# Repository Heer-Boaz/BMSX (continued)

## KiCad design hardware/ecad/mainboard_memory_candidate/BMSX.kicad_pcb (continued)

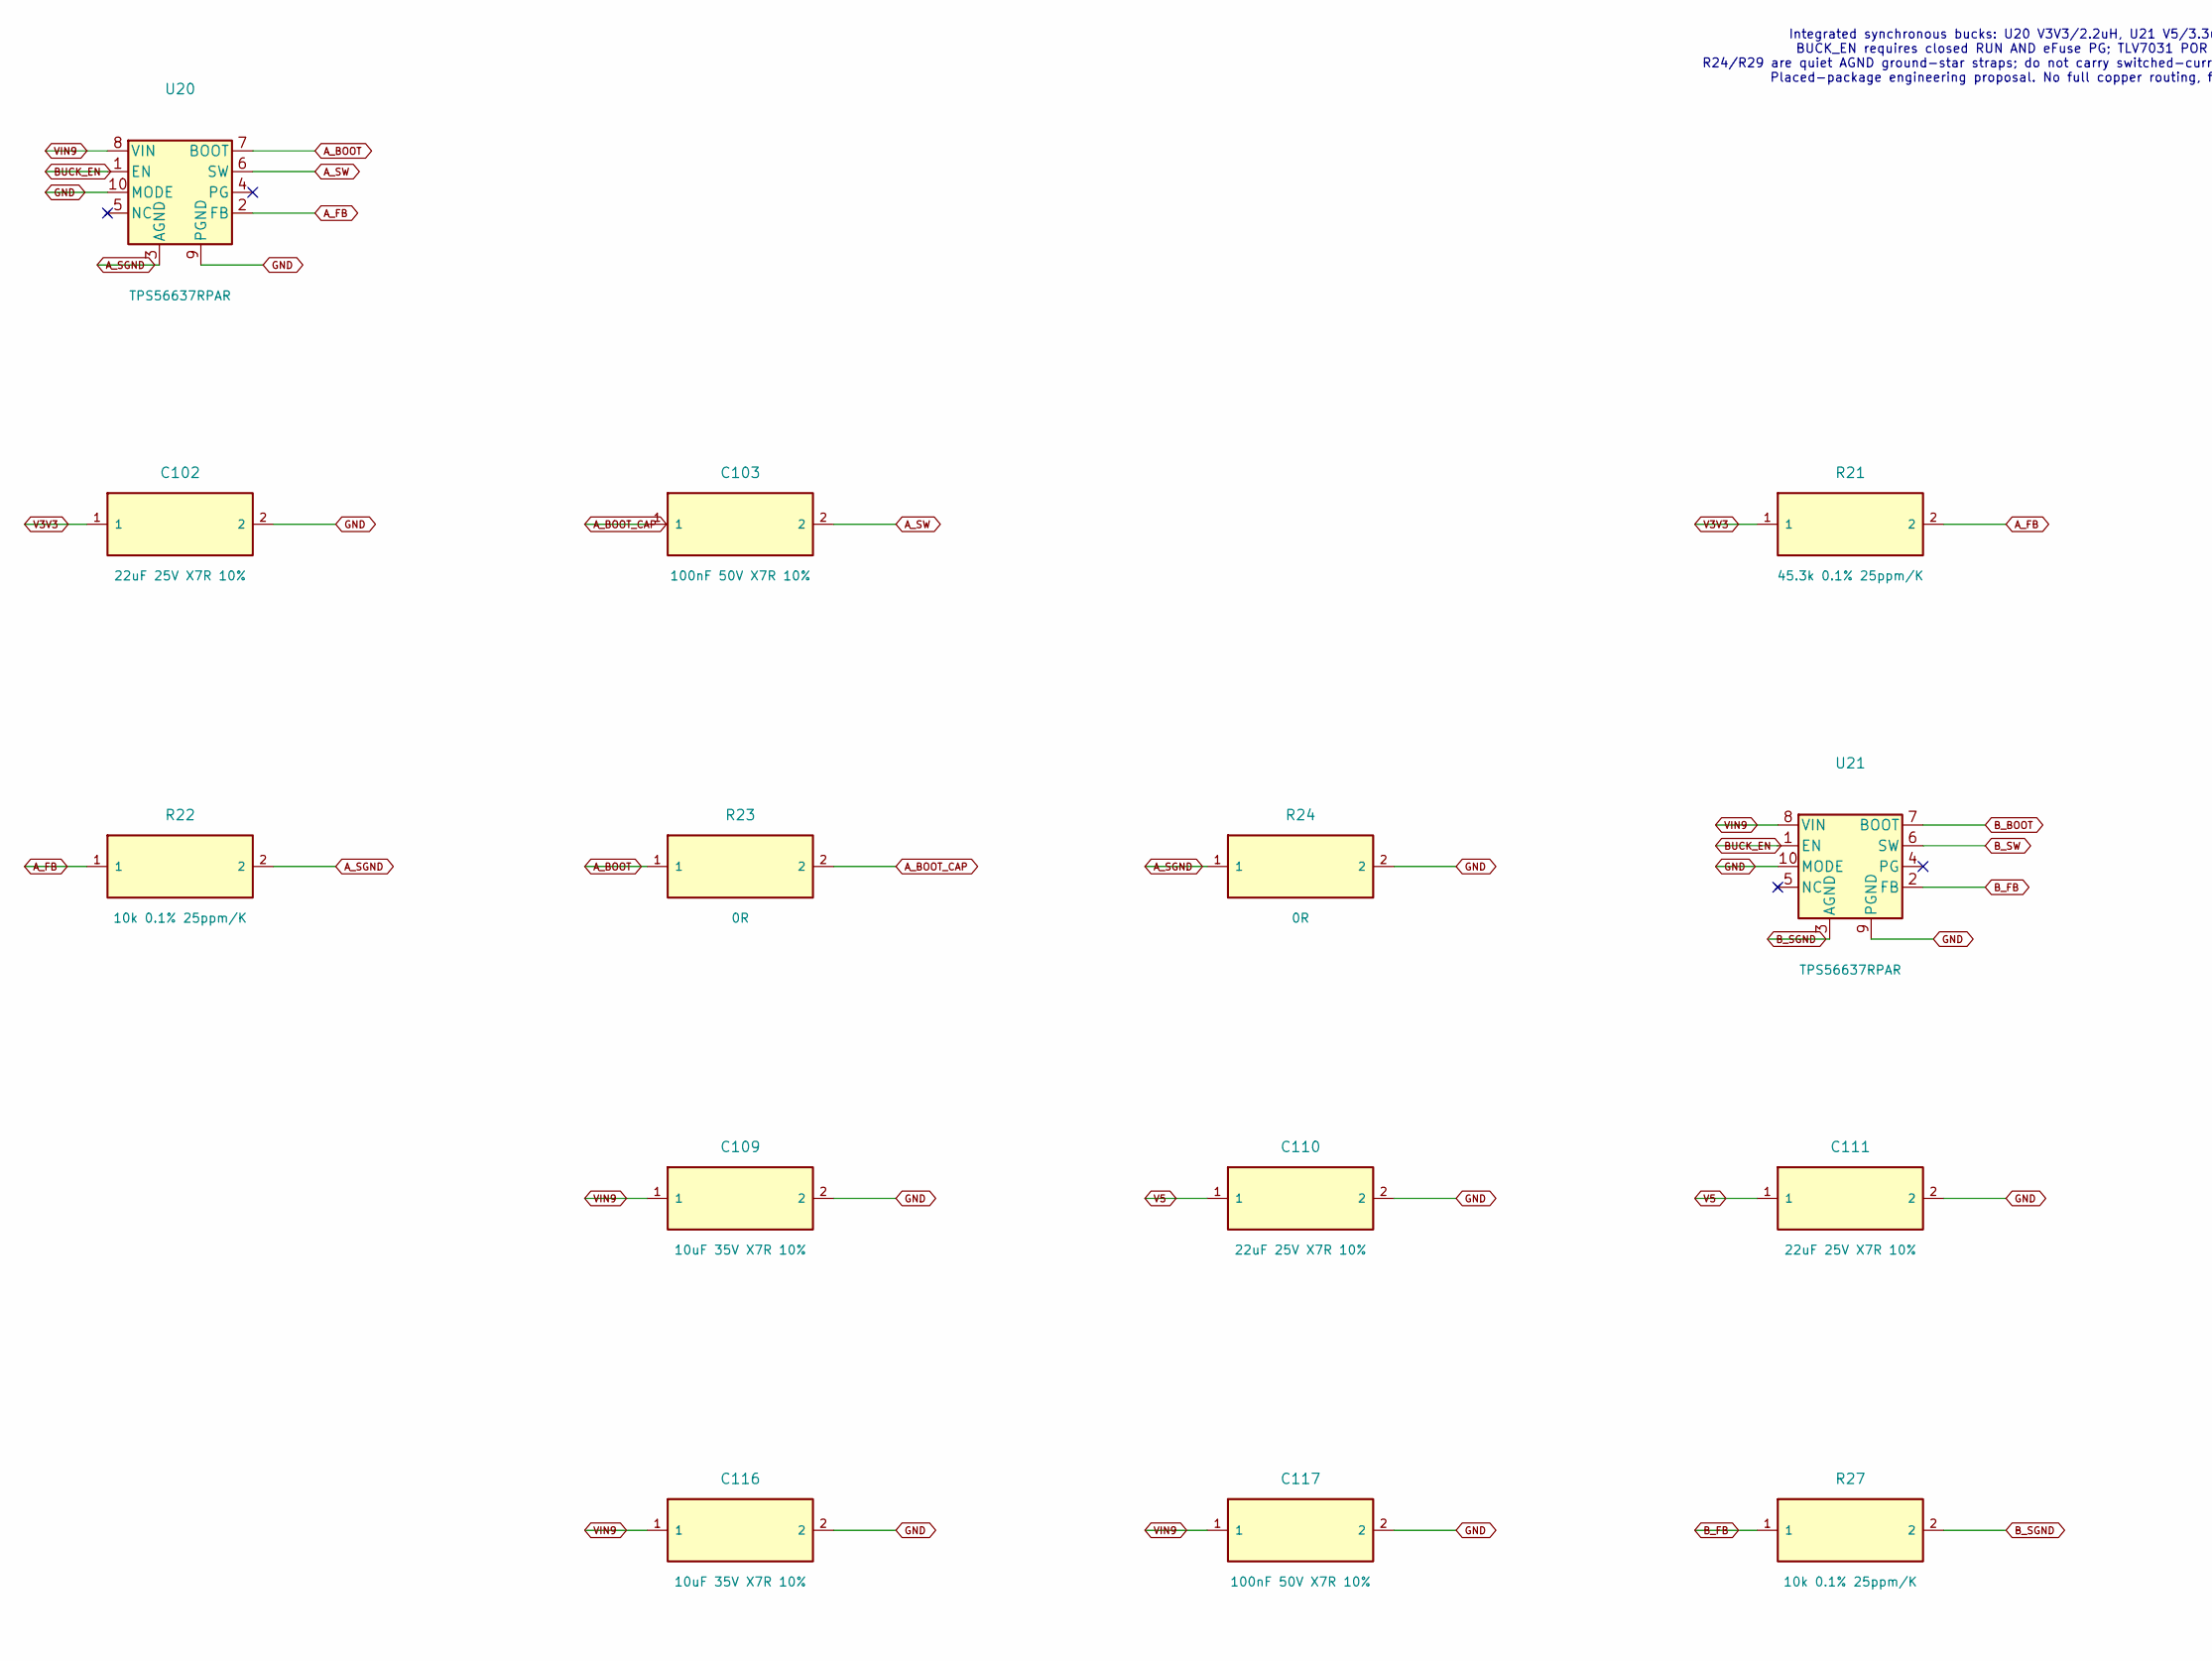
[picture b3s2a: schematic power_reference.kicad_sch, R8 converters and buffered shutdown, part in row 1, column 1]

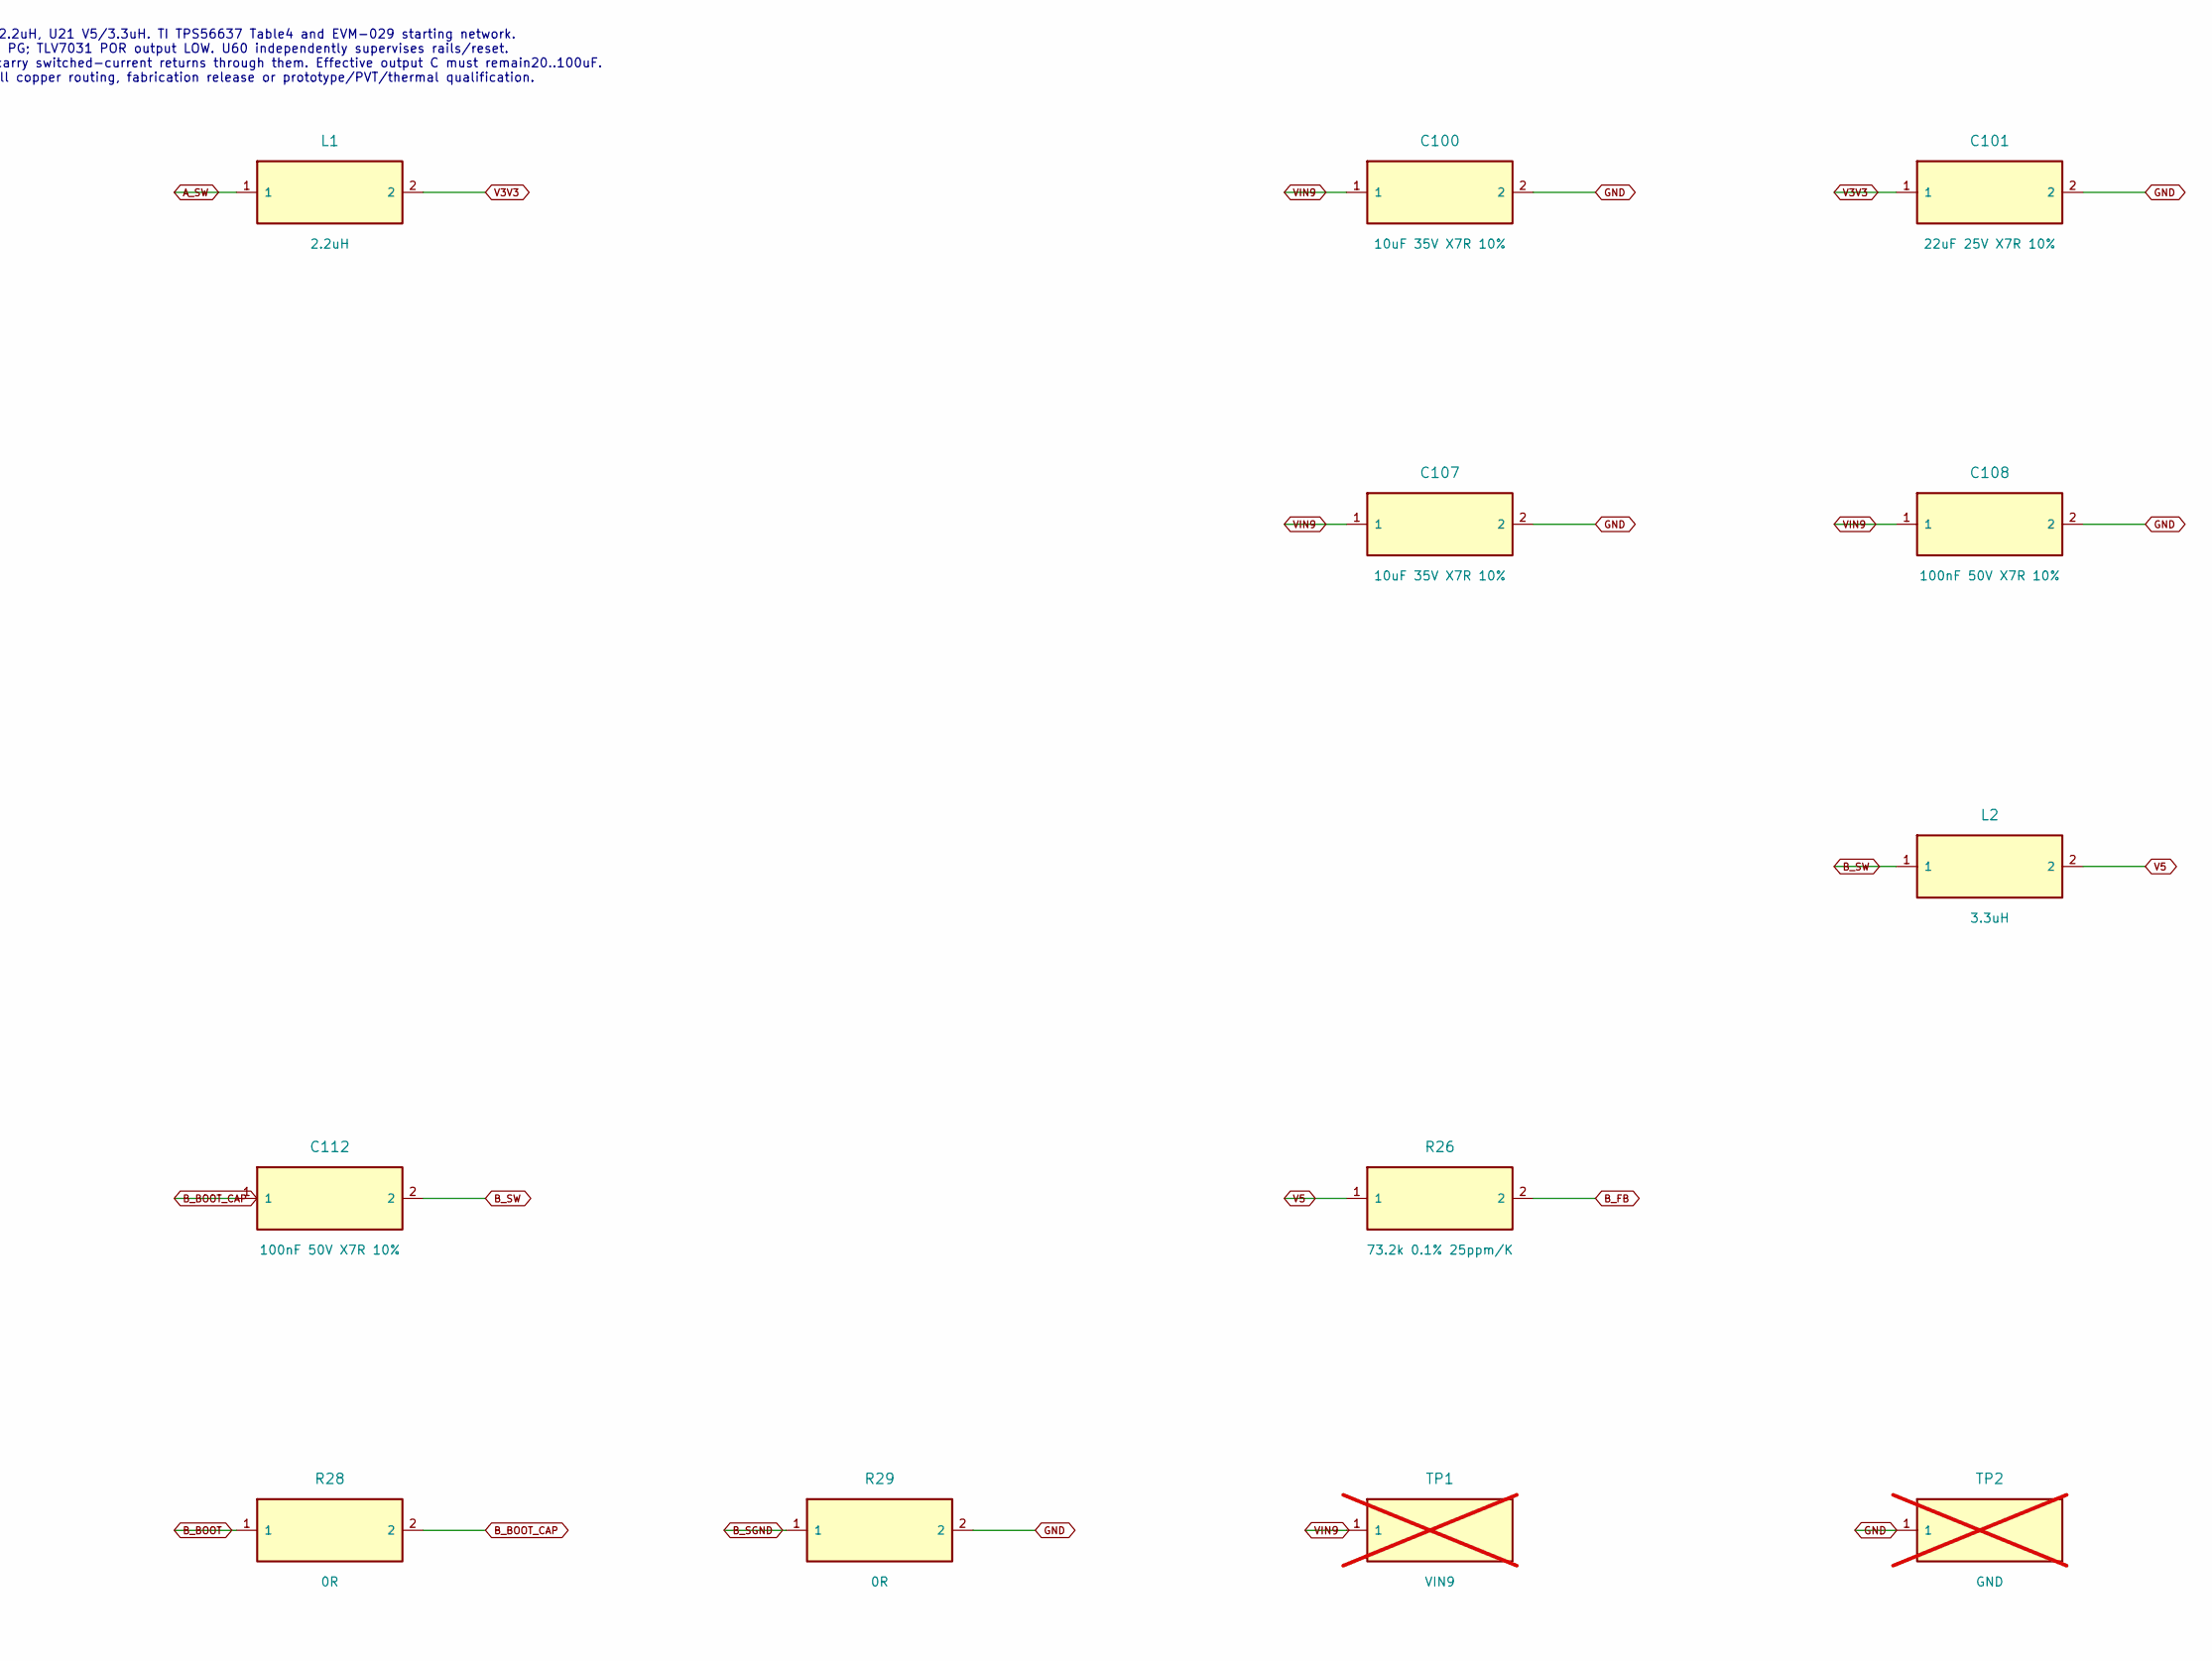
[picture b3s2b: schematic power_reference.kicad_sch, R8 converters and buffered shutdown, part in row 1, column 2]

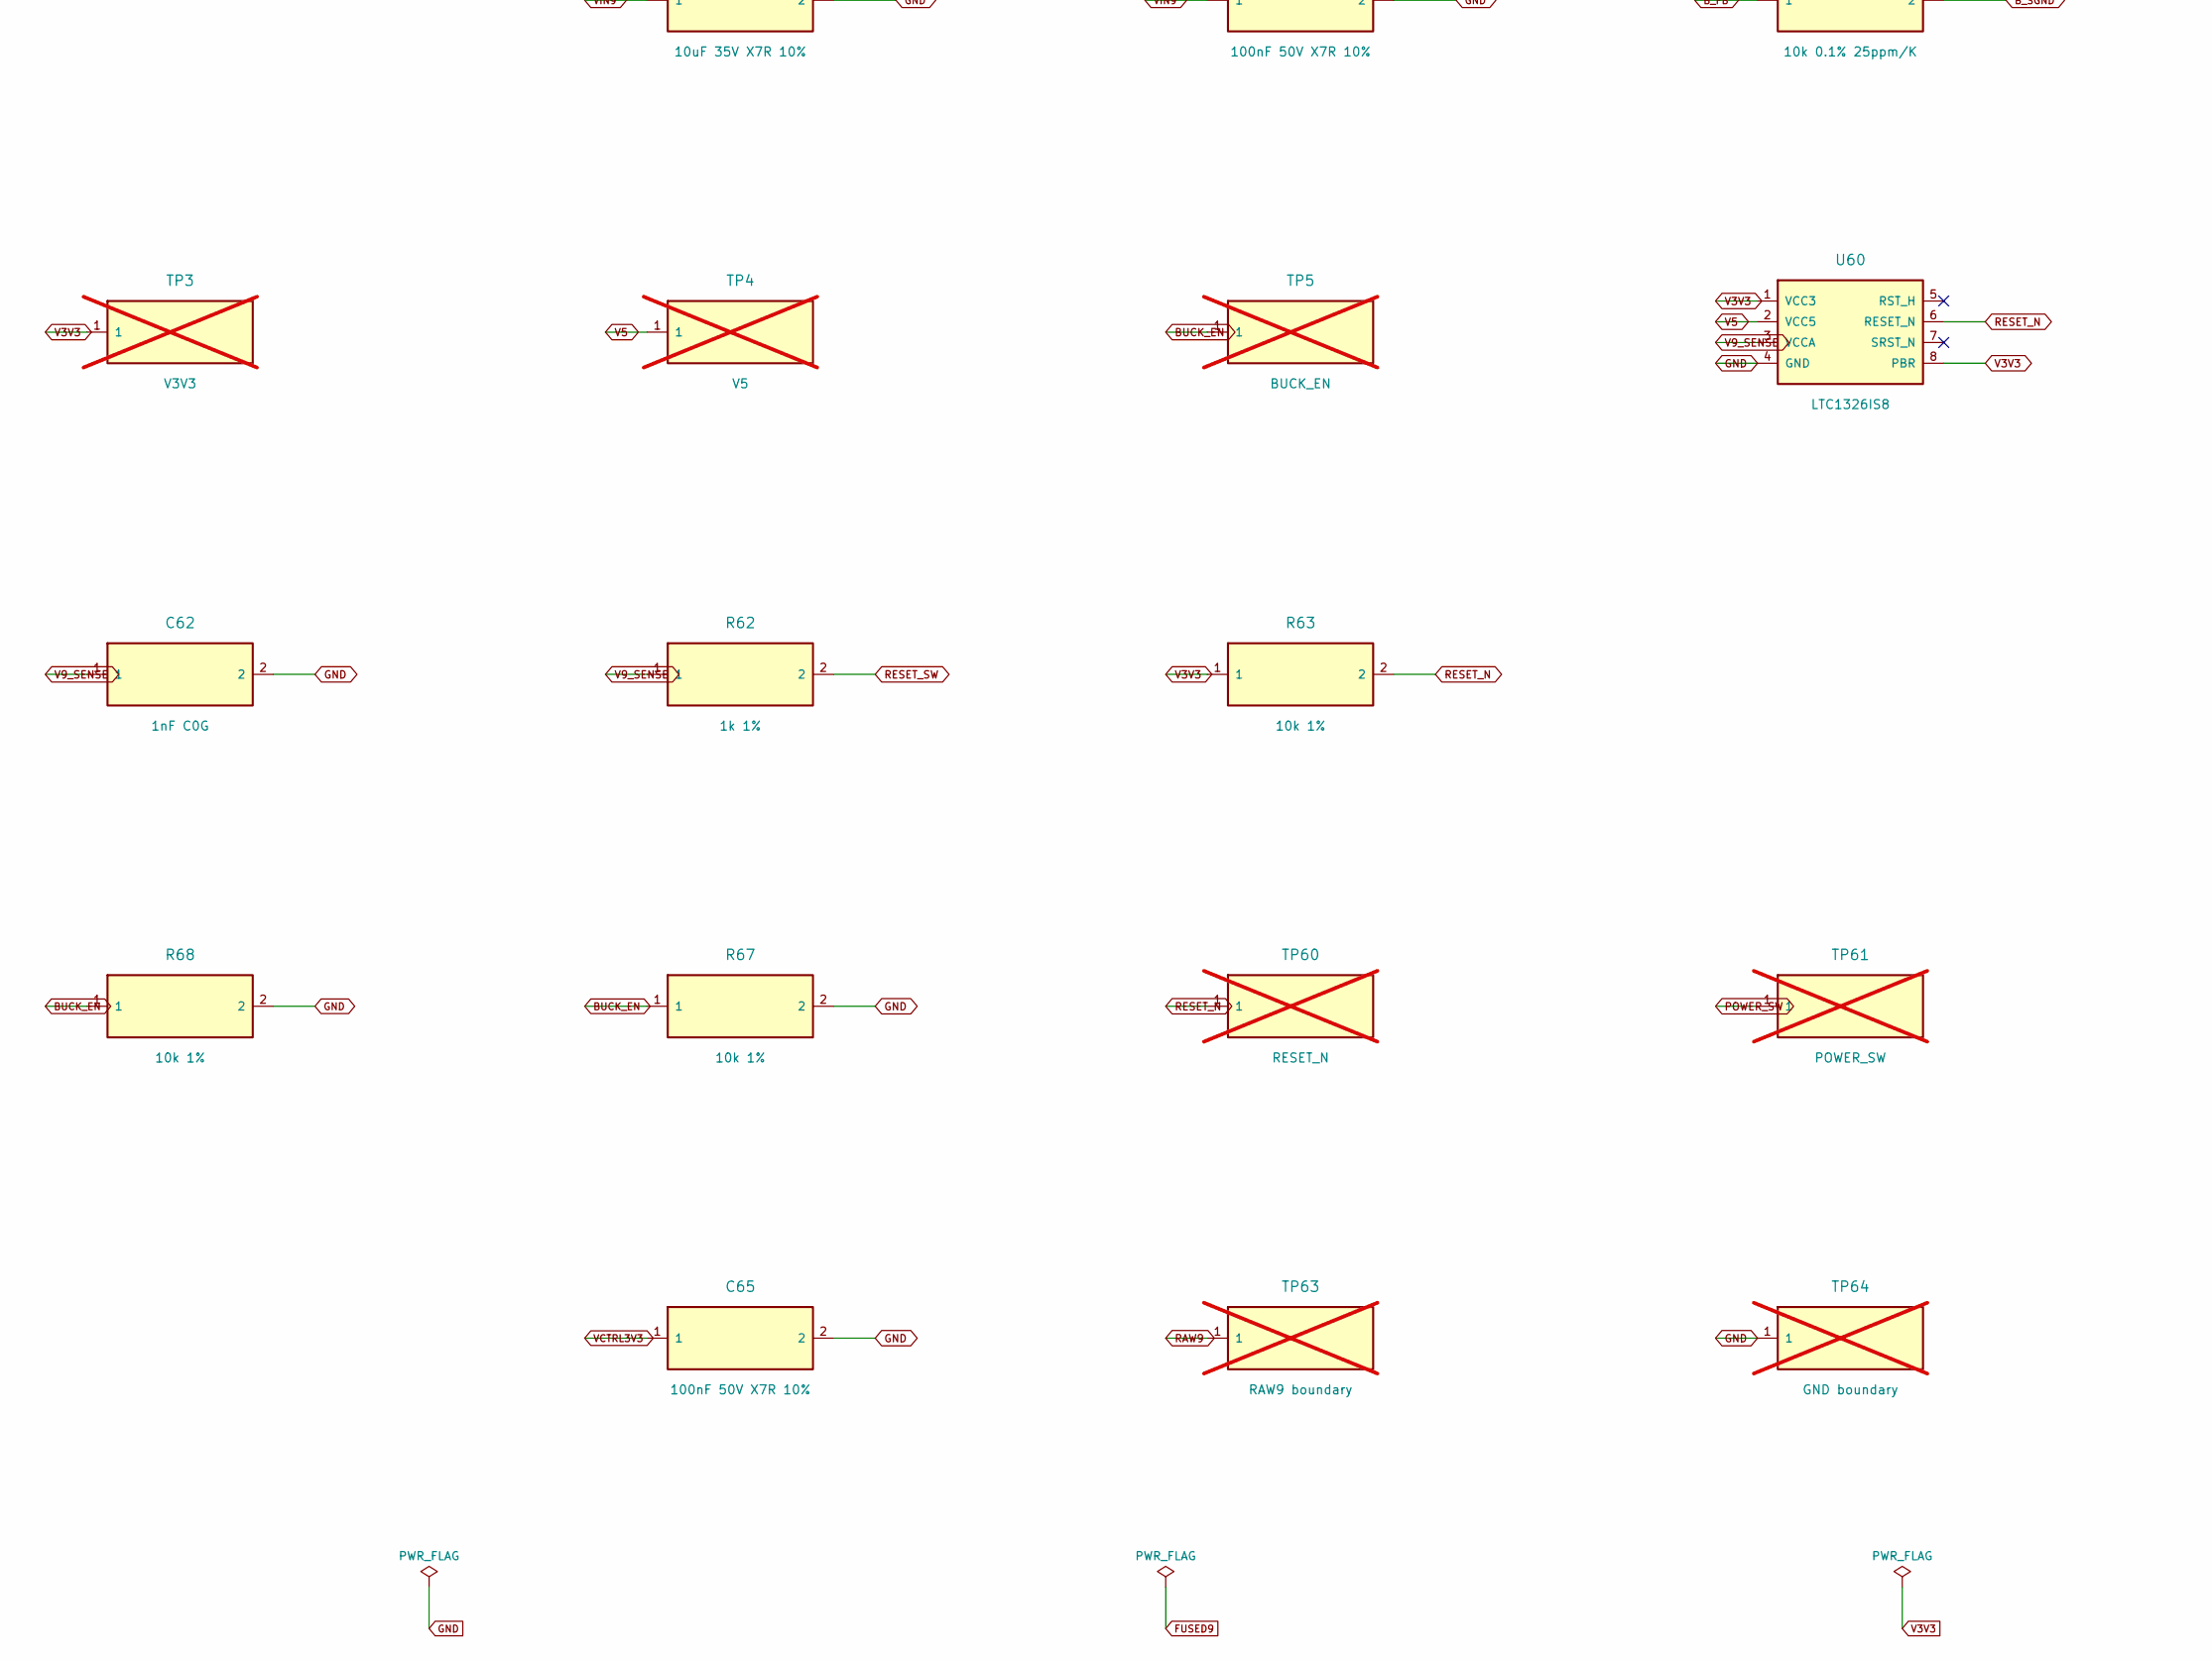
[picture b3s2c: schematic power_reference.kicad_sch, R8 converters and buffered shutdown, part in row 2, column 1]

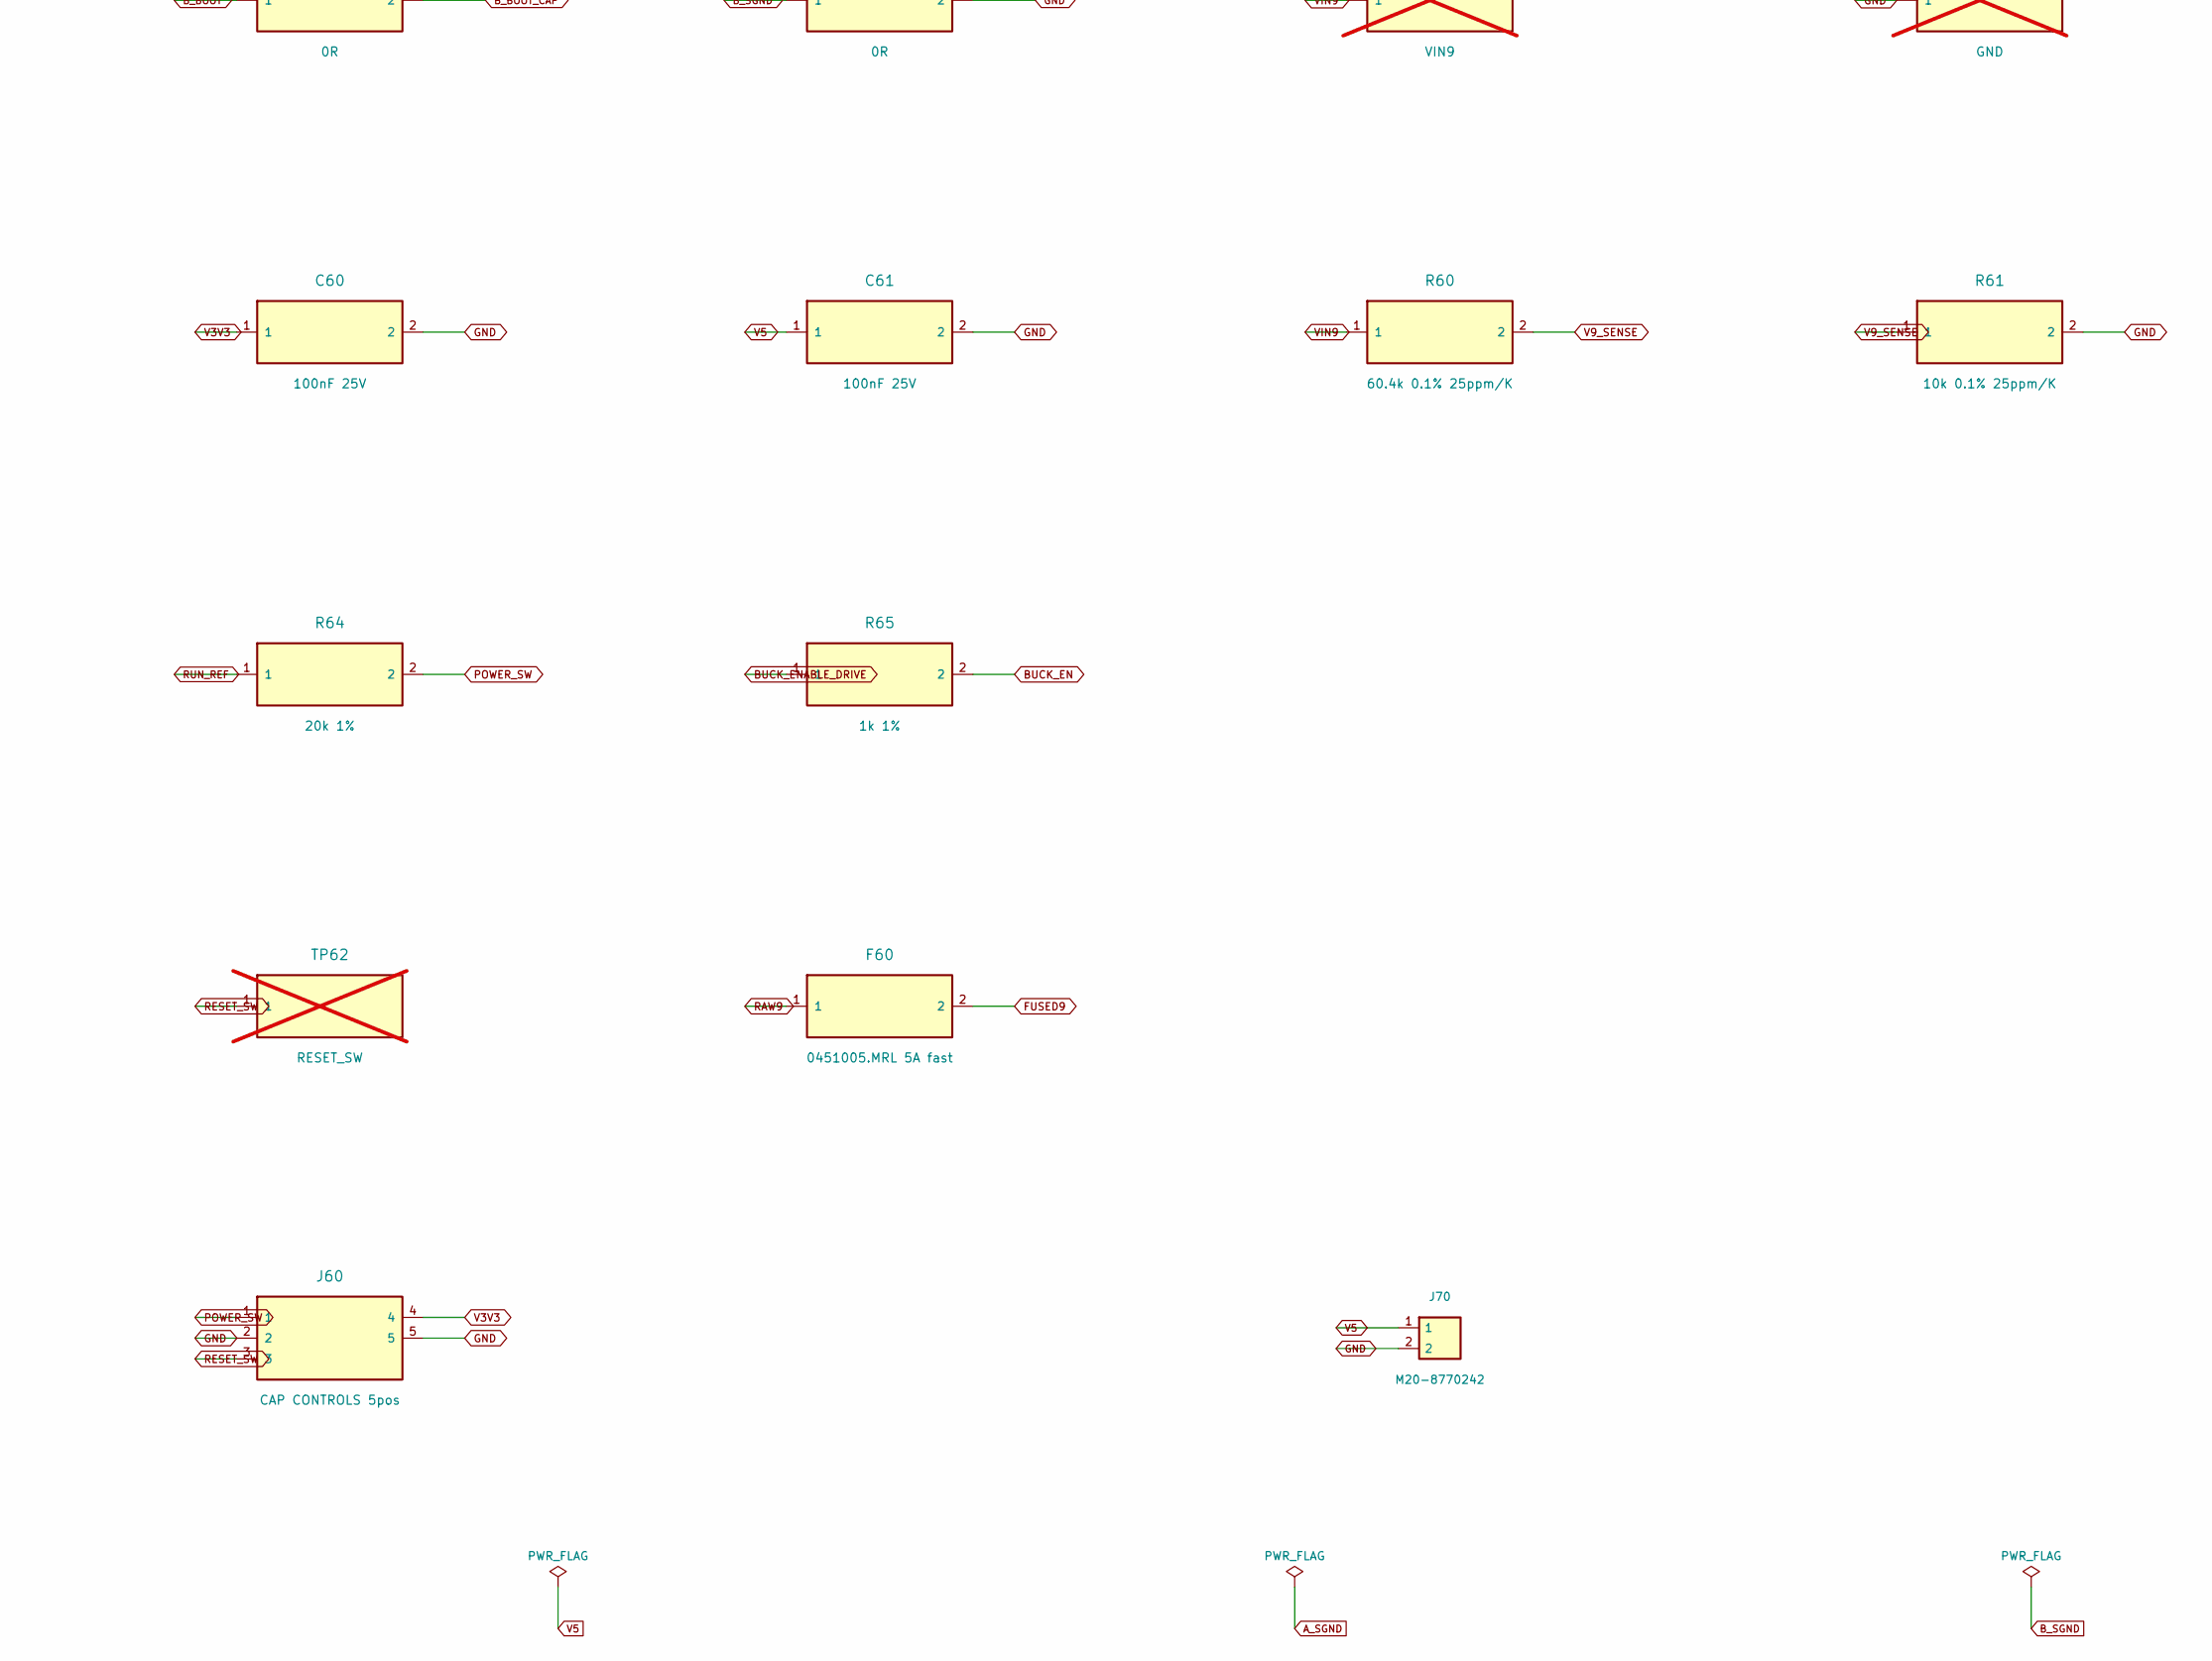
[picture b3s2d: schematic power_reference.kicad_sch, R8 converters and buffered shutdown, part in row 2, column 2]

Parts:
C60, C61: 100nF 25V; CL10B104KA8NNNC_retained_0603; MPN CL10B104KA8NNNC
C62: 1nF C0G; CL10C102JB8NNNC_retained_0603; MPN CL10C102JB8NNNC
C65: 100nF 50V X7R 10%; CL21B104KBCNNNC; MPN CL21B104KBCNNNC
C100, C107, C109, C116: 10uF 35V X7R 10%; C_1210_3225Metric; MPN GRM32ER7YA106KA12L
C101, C102, C110, C111: 22uF 25V X7R 10%; C_1210_3225Metric; MPN GRM32ER71E226KE15L
C103, C108, C112, C117: 100nF 50V X7R 10%; C_0603_1608Metric; MPN 885012206095
F60: 0451005.MRL 5A fast; F60
J60: CAP CONTROLS 5pos; J60; MPN M20-9770542
J70: M20-8770242; Harwin_M20-8770242; MPN M20-8770242
L1: 2.2uH; L_Vishay_IHLP-3232; MPN IHLP3232DZER2R2M11
L2: 3.3uH; L_Vishay_IHLP-3232; MPN IHLP3232DZER3R3M11
R21: 45.3k 0.1% 25ppm/K; TNPW0603_Vishay_28950; MPN TNPW060345K3BEEA
R22, R27, R61: 10k 0.1% 25ppm/K; TNPW0603_Vishay_28950; MPN TNPW060310K0BEEA
R23, R24, R28, R29: 0R; Yageo_RC0603_retained; MPN CRCW06030000Z0EA
R26: 73.2k 0.1% 25ppm/K; TNPW0603_Vishay_28950; MPN TNPW060373K2BEEA
R60: 60.4k 0.1% 25ppm/K; TNPW0603_Vishay_28950; MPN TNPW060360K4BEEA
R62, R65: 1k 1%; Yageo_RC0603_retained; MPN RC0603FR-071KL
R63, R67, R68: 10k 1%; Yageo_RC0603_retained; MPN RC0603FR-0710KL
R64: 20k 1%; Yageo_RC0603_retained; MPN RC0603FR-0720KL
TP1: VIN9; TP1; not fitted
TP2: GND; TP2; not fitted
TP3: V3V3; TP3; not fitted
TP4: V5; TP4; not fitted
TP5: BUCK_EN; TP5; not fitted
TP60: RESET_N; TP60; not fitted
TP61: POWER_SW; TP61; not fitted
TP62: RESET_SW; TP62; not fitted
TP63: RAW9 boundary; TP63; not fitted
TP64: GND boundary; TP64; not fitted
U20, U21: TPS56637RPAR; TPS56637RPAR_RPA0010A; MPN TPS56637RPAR
U60: LTC1326IS8; LTC1326IS8_PBF_S8_retained_IPC; MPN LTC1326IS8#PBF

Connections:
A_BOOT: R23.1, U20.7 (BOOT)
A_BOOT_CAP: C103.1, R23.2
A_FB: R21.2, R22.1, U20.2 (FB)
A_SGND: R22.2, R24.1, U20.3 (AGND)
A_SW: C103.2, L1.1, U20.6 (SW)
BUCK_EN: R65.2, R67.1, R68.1, TP5.1, U20.1 (EN), U21.1 (EN)
BUCK_ENABLE_DRIVE: R65.1; also elsewhere on the board
B_BOOT: R28.1, U21.7 (BOOT)
B_BOOT_CAP: C112.1, R28.2
B_FB: R26.2, R27.1, U21.2 (FB)
B_SGND: R27.2, R29.1, U21.3 (AGND)
B_SW: C112.2, L2.1, U21.6 (SW)
FUSED9: F60.2; also elsewhere on the board
GND: C60.2, C61.2, C62.2, C65.2, C100.2, C101.2, C102.2, C107.2, C108.2, C109.2, C110.2, C111.2, C116.2, C117.2, J60.2, J60.5, J70.2, R24.2, R29.2, R61.2, R67.2, R68.2, TP2.1, TP64.1, U20.9 (PGND), U20.10 (MODE), U21.9 (PGND), U21.10 (MODE), U60.4 (GND); also elsewhere on the board
POWER_SW: J60.1, R64.2, TP61.1
RAW9: F60.1, TP63.1; also elsewhere on the board
RESET_N: R63.2, TP60.1, U60.6 (RESET_N); also elsewhere on the board
RESET_SW: J60.3, R62.2, TP62.1
RUN_REF: R64.1; also elsewhere on the board
V3V3: C60.1, C101.1, C102.1, J60.4, L1.2, R21.1, R63.1, TP3.1, U60.1 (VCC3), U60.8 (PBR); also elsewhere on the board
V5: C61.1, C110.1, C111.1, J70.1, L2.2, R26.1, TP4.1, U60.2 (VCC5); also elsewhere on the board
V9_SENSE: C62.1, R60.2, R61.1, R62.1, U60.3 (VCCA)
VCTRL3V3: C65.1; also elsewhere on the board
VIN9: C100.1, C107.1, C108.1, C109.1, C116.1, C117.1, R60.1, TP1.1, U20.8 (VIN), U21.8 (VIN); also elsewhere on the board

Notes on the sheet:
Integrated synchronous bucks: U20 V3V3/2.2uH, U21 V5/3.3uH. TI TPS56637 Table4 and EVM-029 starting network. BUCK_EN requires closed RUN AND eFuse PG; TLV7031 POR output LOW. U60 independently supervises rails/reset. R24/R29 are quiet AGND ground-star straps; do not carry switched-current returns t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
